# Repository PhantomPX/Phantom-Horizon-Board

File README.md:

# Phantom-Horizon-Board

An overpowered dev board with dual MCU, ESP32 for wireless connection and STM32 for GPIOs and ADC pins.

It's a great dev board for testing & prototyping for projects using motors.
I'll be using the board to prototype my upcoming project [Phantom Strata](https://github.com/PhantomPX/Phantom-Horizon-Board) CNC machine

## Schematic

## PCB Layout

4 layers PCB - Signal-3.3V-GND-Signal

| Top layer | Bottom layer |
| --------- | ------------ |
| |  |
|  |  |

## PCB 

<table>
  <tr>
    <td></td>
    <td></td>
  </tr>
</table>

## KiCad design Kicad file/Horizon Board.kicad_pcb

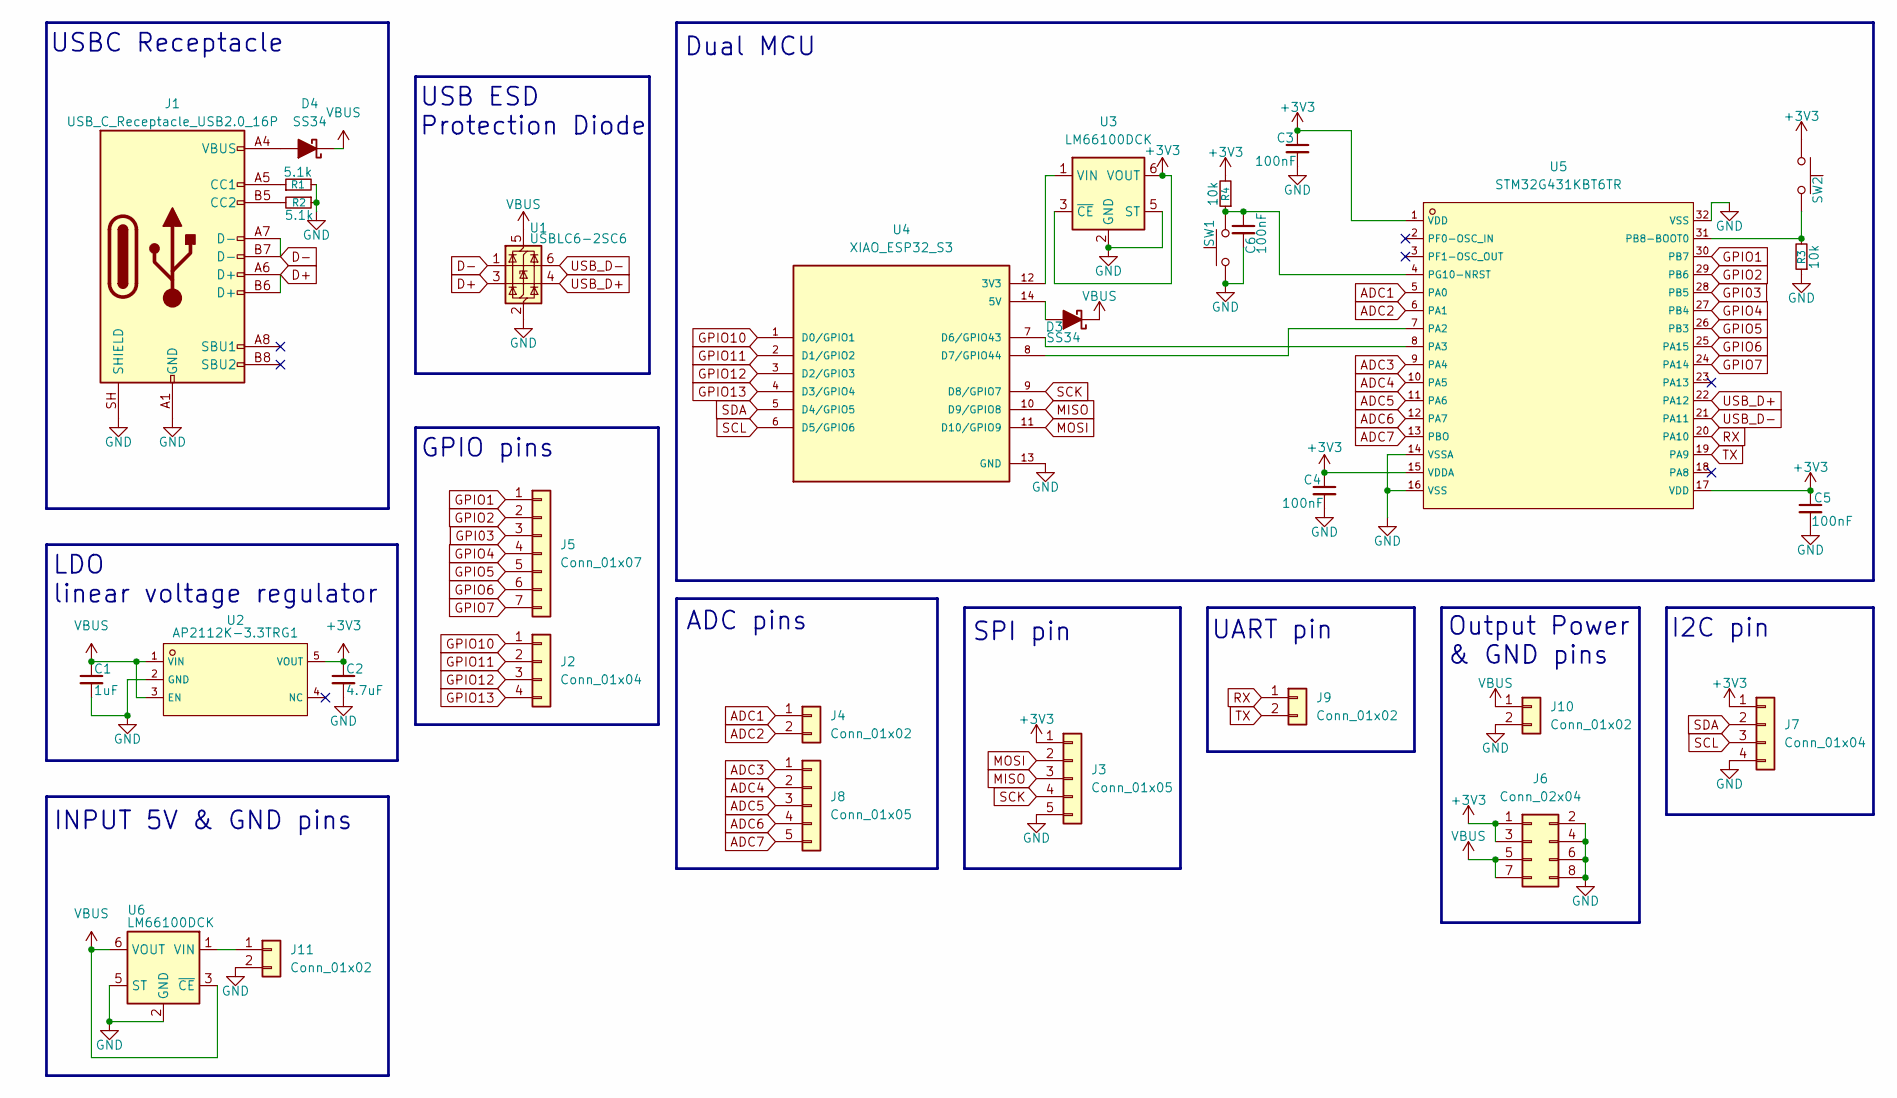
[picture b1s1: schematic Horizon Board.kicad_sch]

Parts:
C1: 1uF; C_0603_1608Metric_Pad1.08x0.95mm_HandSolder
C2: 4.7uF; C_0603_1608Metric_Pad1.08x0.95mm_HandSolder
C3, C4, C5, C6: 100nF; C_0402_1005Metric_Pad0.74x0.62mm_HandSolder
D3, D4: SS34; D_SMC
J1: USB_C_Receptacle_USB2.0_16P; USB_C_Receptacle_GCT_USB4085
J2, J7: Conn_01x04; PinSocket_1x04_P2.54mm_Vertical; Part Number 1-0401FBV0T
J3, J8: Conn_01x05; PinSocket_1x05_P2.54mm_Vertical
J4, J9, J10, J11: Conn_01x02; PinSocket_1x02_P2.54mm_Vertical
J5: Conn_01x07; PinSocket_1x07_P2.54mm_Vertical
J6: Conn_02x04; PinSocket_2x04_P2.54mm_Vertical; Part Number 1-0802FBV0T
R1, R2: 5.1k; R_0402_1005Metric_Pad0.72x0.64mm_HandSolder
R3, R4: 10k; R_0402_1005Metric_Pad0.72x0.64mm_HandSolder
SW1, SW2: SW_Push; SW_SPST_B3U-1000P
U1: USBLC6-2SC6; SOT-23-6
U2: AP2112K-3.3TRG1; C51118_SOT-25-5_L2_9-W1_6-P0_95-LS2_8-BL; LCSC C51118
U3, U6: LM66100DCK; SOT-363_SC-70-6
U4: XIAO_ESP32_S3; MODULE_XIAO_ESP32_S3; MPN XIAO ESP32 S3
U5: STM32G431KBT6TR; C5270317_LQFP-32_L7_0-W7_0-P0_80-LS9_0-BL; LCSC C5270317

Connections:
+3V3: C2.1, C3.1, C4.1, C5.1, J3.1, J6.1, J6.3, J7.1, R4.2, SW2.1, U2.5 (VOUT), U3.3 (~CE), U3.6 (VOUT), U5.1 (VDD), U5.15 (VDDA), U5.17 (VDD)
ADC1: J4.1, U5.5 (PA0)
ADC2: J4.2, U5.6 (PA1)
ADC3: J8.1, U5.9 (PA4)
ADC4: J8.2, U5.10 (PA5)
ADC5: J8.3, U5.11 (PA6)
ADC6: J8.4, U5.12 (PA7)
ADC7: J8.5, U5.13 (PBO)
D+: J1.A6 (D+), J1.B6 (D+), U1.3 (I/O2)
D-: J1.A7 (D-), J1.B7 (D-), U1.1 (I/O1)
GND: C1.2, C2.2, C3.2, C4.2, C5.2, C6.2, J1.A1 (GND), J1.A12 (GND), J1.B1 (GND), J1.B12 (GND), J1.SH (SHIELD), J3.5, J6.2, J6.4, J6.6, J6.8, J7.4, J10.2, J11.2, R1.2, R2.1, R3.1, SW1.1, U1.2 (GND), U2.2 (GND), U3.2 (GND), U3.5 (ST), U4.13 (GND), U5.14 (VSSA), U5.16 (VSS), U5.32 (VSS), U6.2 (GND), U6.5 (ST)
GPI03: J5.3, U5.28 (PB5)
GPIO1: J5.1, U5.30 (PB7)
GPIO2: J5.2, U5.29 (PB6)
GPIO4: J5.4, U5.27 (PB4)
GPIO5: J5.5, U5.26 (PB3)
GPIO6: J5.6, U5.25 (PA15)
GPIO7: J5.7, U5.24 (PA14)
GPIO10: J2.1, U4.1 (D0/GPIO1)
GPIO11: J2.2, U4.2 (D1/GPIO2)
GPIO12: J2.3, U4.3 (D2/GPIO3)
GPIO13: J2.4, U4.4 (D3/GPIO4)
MISO: J3.3, U4.10 (D9/GPIO8)
MOSI: J3.2, U4.11 (D10/GPIO9)
unnamed: D3.2 (A), U4.14 (5V)
unnamed: D4.2 (A), J1.A4 (VBUS), J1.A9 (VBUS), J1.B4 (VBUS), J1.B9 (VBUS)
unnamed: J1.A5 (CC1), R1.1
unnamed: J1.B5 (CC2), R2.2
unnamed: J11.1, U6.1 (VIN)
unnamed: U3.1 (VIN), U4.12 (3V3)
unnamed: U4.7 (D6/GPIO43), U5.8 (PA3)
unnamed: U4.8 (D7/GPIO44), U5.7 (PA2)
unnamed: R3.2, SW2.2, U5.31 (PB8-BOOT0)
unnamed: C6.1, R4.1, SW1.2, U5.4 (PG10-NRST)
RX: J9.1, U5.20 (PA10)
SCK: J3.4, U4.9 (D8/GPIO7)
SCL: J7.3, U4.6 (D5/GPIO6)
SDA: J7.2, U4.5 (D4/GPIO5)
TX: J9.2, U5.19 (PA9)
USB_D+: U1.4 (I/O2), U5.22 (PA12)
USB_D-: U1.6 (I/O1), U5.21 (PA11)
VBUS: C1.1, D3.1 (K), D4.1 (K), J6.5, J6.7, J10.1, U1.5 (VBUS), U2.1 (VIN), U2.3 (EN), U6.3 (~CE), U6.6 (VOUT)

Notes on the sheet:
USBC Receptacle
Dual MCU
INPUT 5V & GND pins
USB ESD Protection Diode
Output Power & GND pins
ADC pins
LDO linear voltage regulator
GPIO pins
UART pin
I2C pin
SPI pin

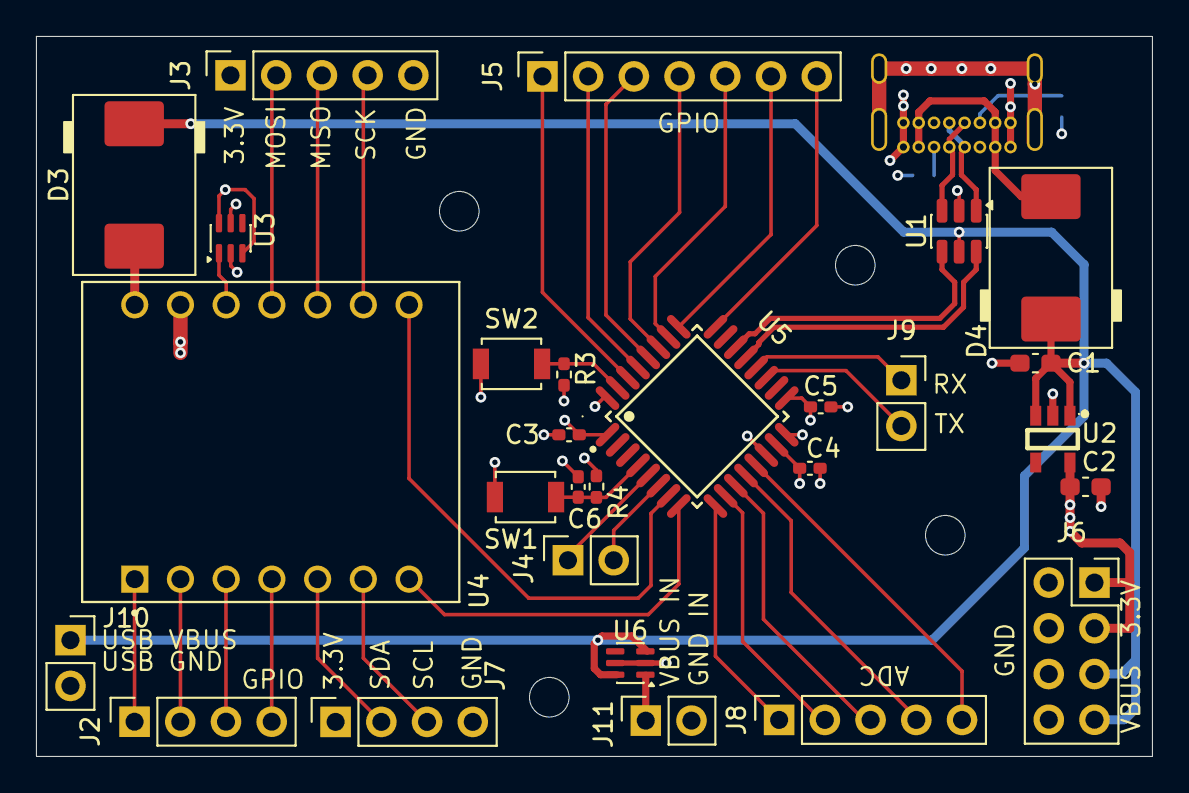
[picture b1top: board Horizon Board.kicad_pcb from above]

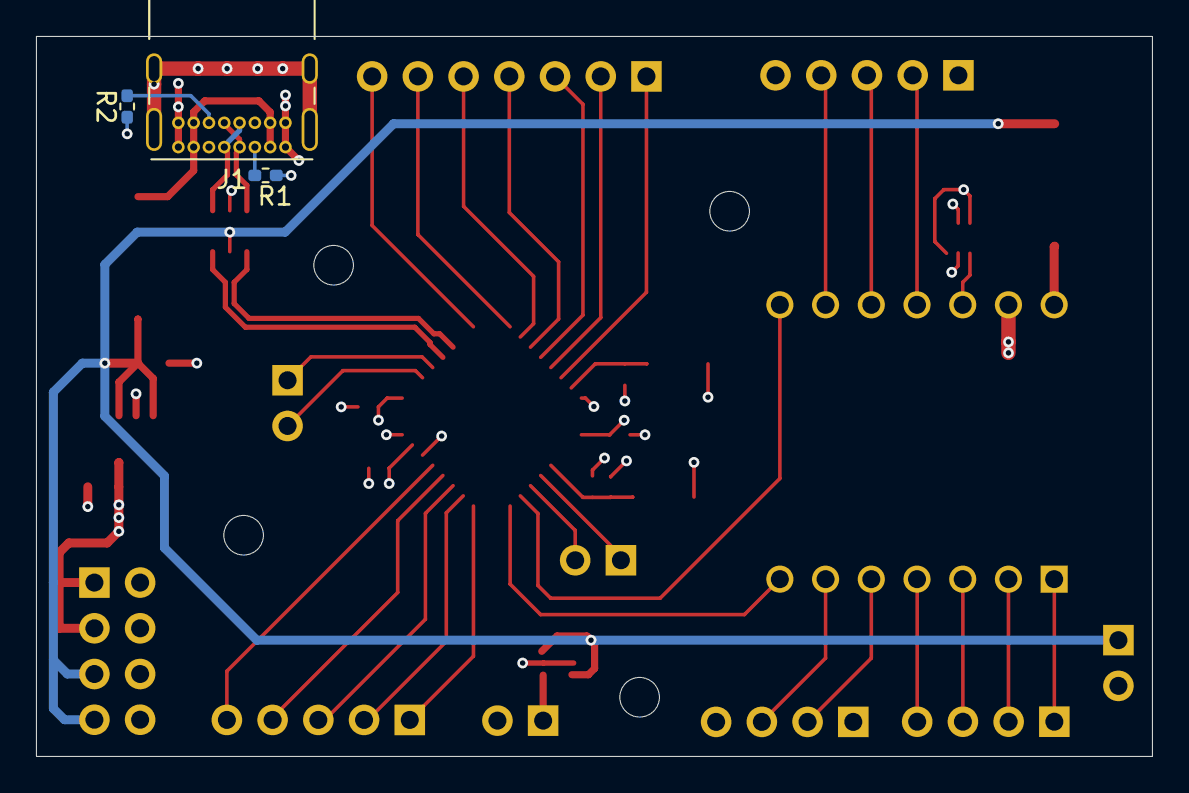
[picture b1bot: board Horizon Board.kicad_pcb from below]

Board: 4 copper layers, 62.0 x 40.0 mm, 31 parts (3 on the bottom side), 42 nets.

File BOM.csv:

Item,Qty,Supplier,Cost/item,Total Cost,link
1uF,1,TaoBao,$0.00,  $0.00  ,https://item.taobao.com/item.htm?from=cart&id=630712731066&m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
4.7uF,1,TaoBao,$0.00,  $0.00  ,https://item.taobao.com/item.htm?from=cart&id=630712731066&m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
100nF,4,TaoBao,$0.00,  $0.00  ,https://item.taobao.com/item.htm?abbucket=0&id=733879274781&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
SS34,2,TaoBao,$0.03, $0.03 ,https://item.taobao.com/item.htm?ali_refid=a3_430620_1006%3A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
USB_C_Receptacle_USB2.0_16P,1,TaoBao,$0.08,  $0.08  ,https://item.taobao.com/item.htm?id=591211481748&mi_id=0000r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
5.1k,2,TaoBao,$0.00,  $0.00  ,https://item.taobao.com/item.htm?id=525633713781&mi_id=0000g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
10k,2,TaoBao,$0.00,  $0.00  ,https://item.taobao.com/item.htm?id=525633713781&mi_id=0000g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
SW_Push,2,TaoBao,$0.10,  $0.20  ,https://item.taobao.com/item.htm?abbucket=20&id=106190013432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
USBLC6-2SC6,1,TaoBao,$0.23,  $0.23  ,https://item.taobao.com/item.htm?id=763430084934&mi_id=0000e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
AP2112K-3.3TRG1,1,TaoBao,$0.55,  $0.55  ,https://intl.taobao.com/sk/_b.OcKv5a
LM66100DCK,2,TaoBao,$0.01, $0.01 ,https://item.taobao.com/item.htm?abbucket=20&id=829363990282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
XIAO_ESP32_S3,1,AliXpress,$5.45, $5.45 ,https://www.aliexpress.com/item/1005006987905528.html?src=go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
STM32G431KBT6TR,1,TaoBao,$1.81, $1.81 ,https://item.taobao.com/item.htm?abbucket=20&id=812217501130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
PCB,1,JLCPCB,$6.00, $6.00 ,jlcpcb.com
,,,,,
Total,,,,$14.31,
